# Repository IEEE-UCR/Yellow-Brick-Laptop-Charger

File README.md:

Yellow-Brick-Laptop-Charger
===========================

Because why not charge your laptop from a giant, scary yellow brick lipo?

Made with KiCAD nightly.

Design Specifics
----------------
The most important things (the soft start and such are all set to the Ti
reference values) are the UVLO and output voltage divider.

The UVLO circuit is set to around 36V (3.0V per cell in a 12S configuration).
It is noted that paranoid users can use a 10S lipo (which would cut off at
around 3.6V per cell).

The output voltage divider is set at 19V.  This is enough to power most devices.  It is crucial that a 5V buck converter be added for USB devices (or else they
might blow up.)

BOM
---
The Bill of Materials is actually pretty hard to generate from the nightly
version of kicad that Brandon is running.
So, the XML file actually has all of the materials in it.
Most of the components are 0805 sized, except for the 1μF capacitors which are
(and don't quote me on this) 1206 sized.

Here is a Digi-key link for enough parts to prototype three of these boards.
http://www.digikey.com/short/749jqc  These include the test points.  Feel
free to modify things as fit.  Do note that these BOMs do not contain the
LEDs for indicating that the board is powered.  (Or at least I don't think
they do...)

PCB
---
There is a dirty PCBs order that I placed a while ago.
Here is the "share" link.
http://dirtypcbs.com/view.php?share=4775&accesskey=4ce9e3b627f7e16a034119993f725ab9

You should be able to order the protopack pretty easily through this link.
Beware that these may not be the most current PCBs.

Important Notes
---------------
There are some specific packages that are not included in the KiCAD libraries,
but all of those should be included within this package.

Note that this.pretty contains component footprints associated to this build.
Note that the schematic symbols associated with this build aren't very neatly
organized in a separate folder.

The inductor specified in the Digikey order is not entirely correct.  The design (later on) was used with a T106-2 core from Micrometals with the appropriate number of turns.  Use an online calculator.

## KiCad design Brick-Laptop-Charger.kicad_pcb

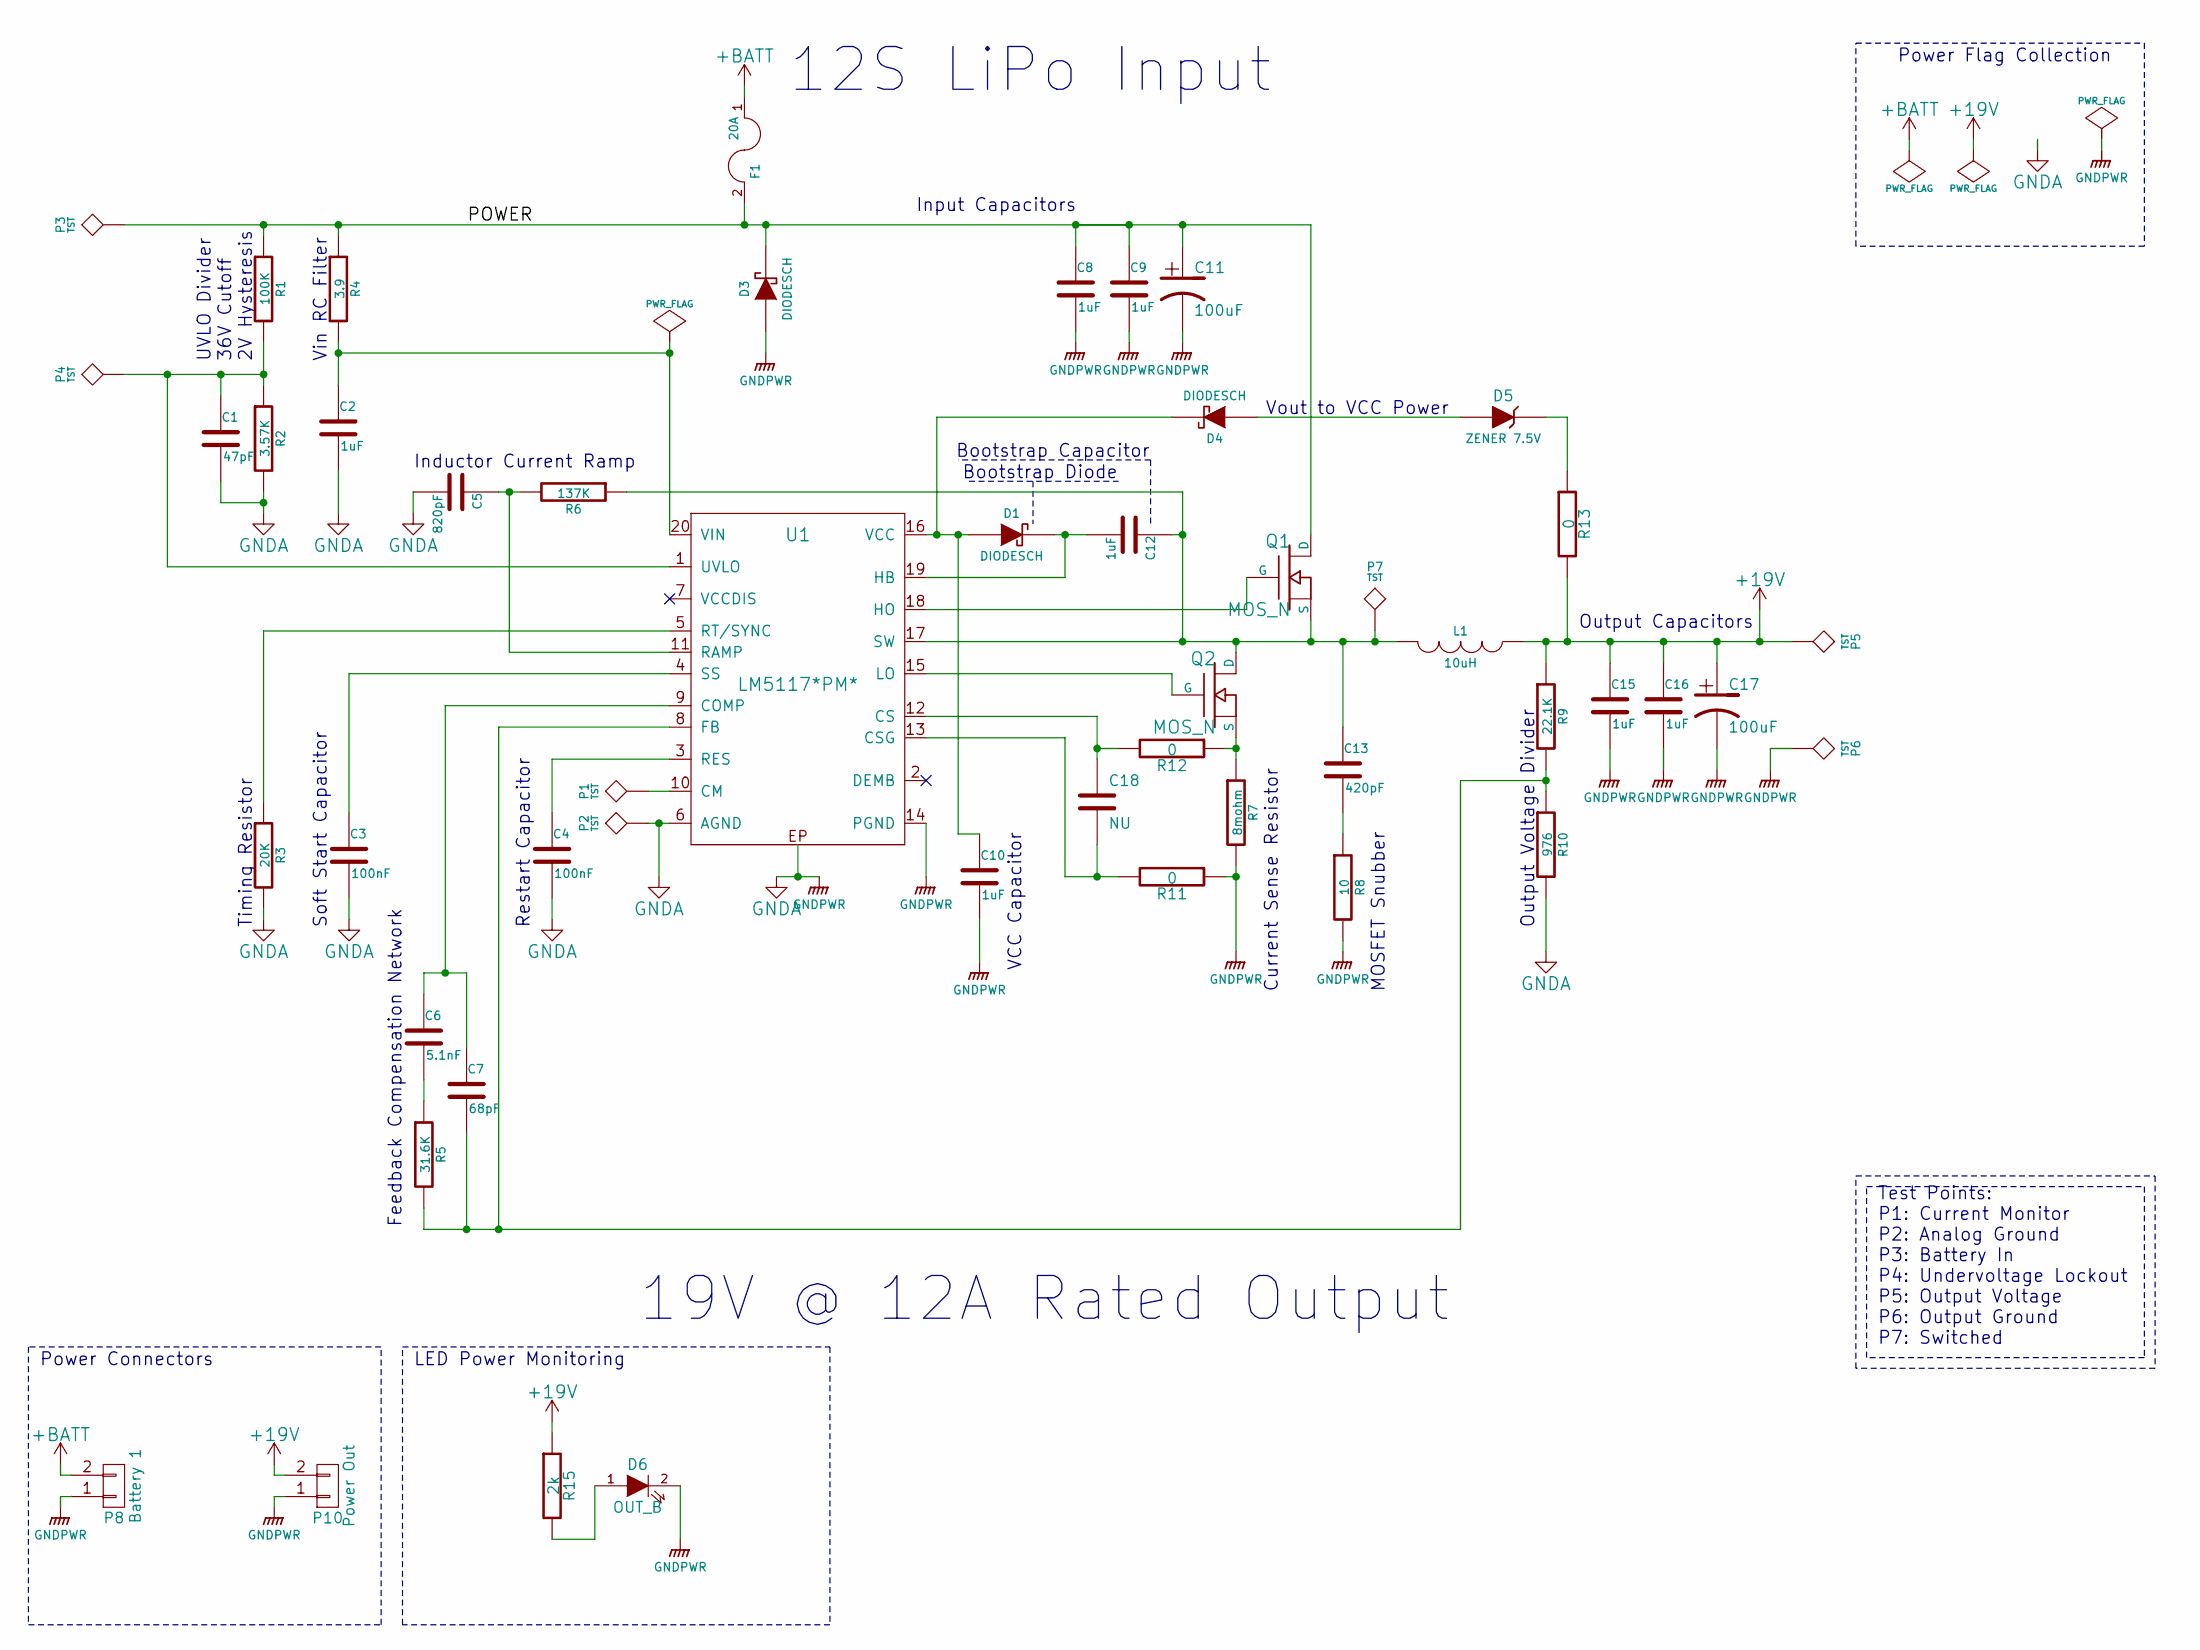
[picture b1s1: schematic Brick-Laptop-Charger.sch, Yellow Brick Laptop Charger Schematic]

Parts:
C1: 47pF; C_0805
C2, C8, C9, C10, C12, C15, C16: 1uF; C_1206
C3, C4: 100nF; C_0805
C5: 820pF; C_0805
C6: 5.1nF; C_0805
C7: 68pF; C_0805
C11: 100uF; c_elec_10x10
C13: 420pF; C_0805
C17: 100uF; c_elec_6.3x7.7
C18: NU; C_0805
D1, D3, D4: DIODESCH; Diode-SMB_Standard
D5: ZENER 7.5V; Diode-SMB_Standard
D6: OUT_B; LED-0805
F1: 20A; PC_Auto_Fuse_Holder
L1: 10uH; Toroidal
P1, P2, P3, P4, P5, P6, P7: TST; TP
P8: Battery 1; BIG_CONN
P10: Power Out; BIG_CONN
Q1, Q2: MOS_N; PQFN-8-GDS_IRF_B_5mmx6mm
R1: 100K; R_0805
R2: 3.57K; R_0805
R3: 20K; R_0805
R4: 3.9; R_0805
R5: 31.6K; R_0805
R6: 137K; R_0805
R7: 8mohm; R_2512
R8: 10; R_0805
R9: 22.1K; R_0805
R10: 976; R_0805
R11, R12, R13: 0; R_0805
R15: 2k; R_0805
U1: LM5117*PM*; SSOP-20-1EP_4.4x6.5mm_Pitch0.65mm

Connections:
+19V: C15.1, C16.1, C17.1, L1.1, P5.1, P10.2, R9.1, R13.2, R15.1
+BATT: F1.1, P8.2
/POWER: C8.1, C9.1, C11.1, D3.2 (K), F1.2, P3.1, Q1.D, R1.1, R4.1; also elsewhere on the board
GNDA: C1.2, C2.2, C3.2, C4.2, C5.2, C8.2, C9.2, C10.2, C11.2, C15.2, C16.2, C17.2, D3.1 (A), D6.2 (K), P2.1, P6.1, P8.1, P10.1, R2.2, R3.2, R7.2, R8.2, R10.2, R11.1, U1.6 (AGND), U1.14 (PGND), U1.EP; also elsewhere on the board
unnamed: C1.1, P4.1, R1.2, R2.1, U1.1 (UVLO)
unnamed: C2.1, R4.2, U1.20 (VIN)
unnamed: C3.1, U1.4 (SS)
unnamed: C4.1, U1.3 (RES)
unnamed: C5.1, R6.2, U1.11 (RAMP)
unnamed: C6.1, C7.1, U1.9 (COMP)
unnamed: C6.2, R5.1
unnamed: C7.2, R5.2, R9.2, R10.1, U1.8 (FB)
unnamed: C10.1, D1.1 (A), D4.2 (K), U1.16 (VCC)
unnamed: C12.1, C13.1, L1.2, P7.1, Q1.S, Q2.D, R6.1, U1.17 (SW)
unnamed: C12.2, D1.2 (K), U1.19 (HB)
unnamed: C13.2, R8.1
unnamed: C18.1, R12.2, U1.12 (CS)
unnamed: C18.2, R11.2, U1.13 (CSG)
unnamed: D4.1 (A), D5.1 (A)
unnamed: D5.2 (K), R13.1
unnamed: D6.1 (A), R15.2
unnamed: P1.1, U1.10 (CM)
unnamed: Q1.G, U1.18 (HO)
unnamed: Q2.G, U1.15 (LO)
unnamed: Q2.S, R7.1, R12.1
unnamed: R3.1, U1.5 (RT/SYNC)

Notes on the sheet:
MOSFET Snubber
Current Sense Resistor
UVLO Divider 36V Cutoff 2V Hysteresis
Vin RC Filter
Inductor Current Ramp
Timing Resistor
Soft Start Capacitor
Restart Capacitor
Bootstrap Capacitor
Bootstrap Diode
Output Voltage Divider
Feedback Compensation Network
VCC Capacitor
Power Flag Collection
Power Connectors
Test Points: P1: Current Monitor P2: Analog Ground P3: Battery In P4: Undervoltage Lockout P5: Output Voltage P6: Output Ground P7: Switched
Input Capacitors
Output Capacitors
Vout to VCC Power
19V @ 12A Rated Output
12S LiPo Input
LED Power Monitoring

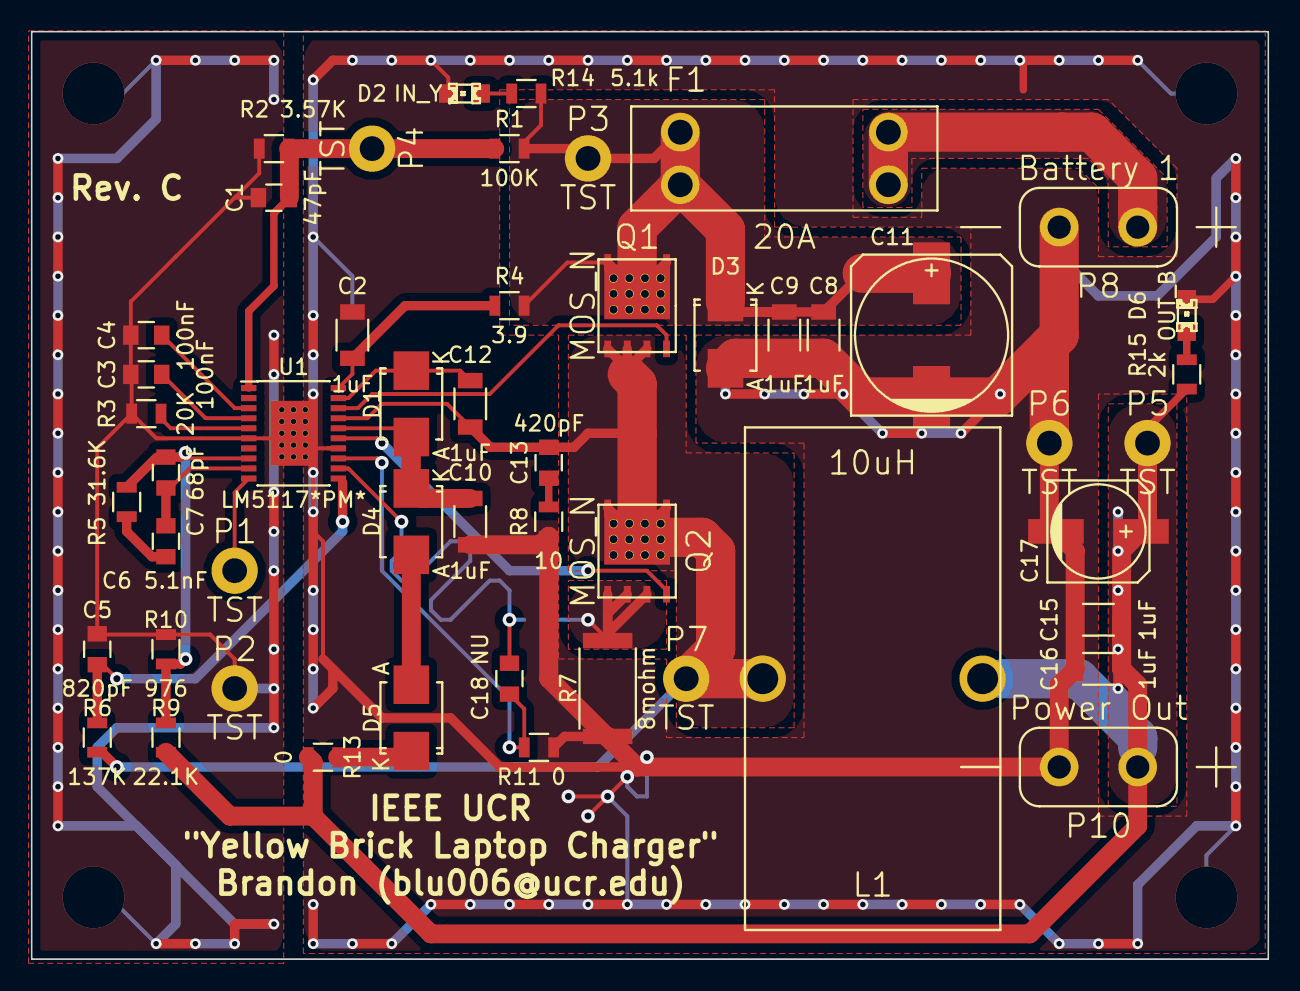
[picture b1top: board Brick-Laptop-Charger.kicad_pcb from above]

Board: 2 copper layers, 80.0 x 60.0 mm, 52 parts (1 on the bottom side), 27 nets.

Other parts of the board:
D2: IN_Y; LED-0805
R14: 5.1k; R_0805

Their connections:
/POWER: R14.1; also elsewhere on the board
GNDA: D2.2; also elsewhere on the board
unnamed: D2.1, R14.2

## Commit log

2015-01-06 Added everything.
2015-01-06 Added readme.
2015-01-06 Modified readme to be more comprehensive.
2015-03-02 Separated analog and power grounds. Most of power current now flows through a separate path from analog circuitry (see exposed trace on bottom of PCB). Reduced capacitive coupling between ground plan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
2015-03-02 Updated readme.
2015-04-01 Modified readme file to current status.
2015-11-04 Moved files, removed backup files, added important notes about inductor selection, added images
2015-11-04 Added pictures.
